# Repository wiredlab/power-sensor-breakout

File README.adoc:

= Power sensor breakout board

Connect common 1S or 2S lithium battery connectors to a load via a INA219 current sensor module.

image::img/pcb-render.png[]

link:power-sensor-breakout/power-sensor-breakout.pdf[Schematic (PDF)^]

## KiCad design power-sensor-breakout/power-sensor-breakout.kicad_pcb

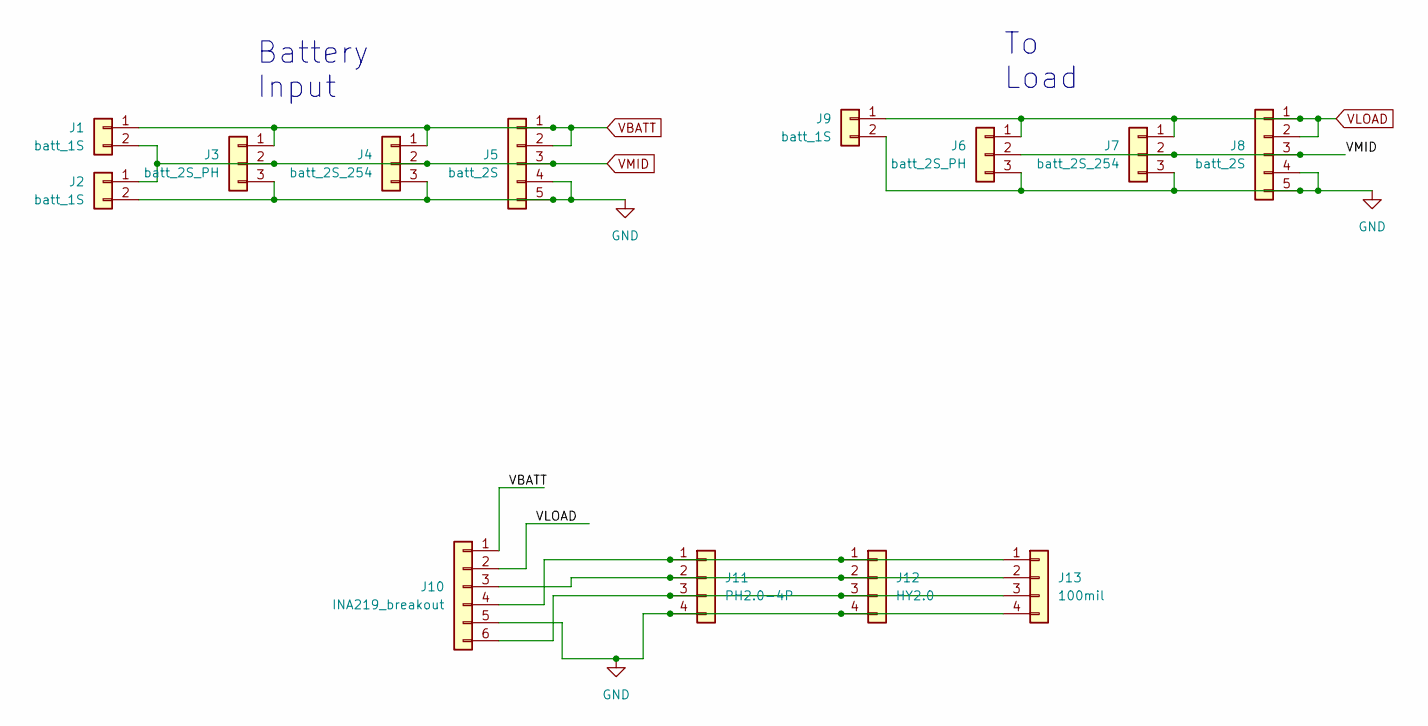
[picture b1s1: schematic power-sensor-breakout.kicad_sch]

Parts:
J1, J2, J9: batt_1S; JST_PH_B2B-PH-K_1x02_P2.00mm_Vertical
J3, J6: batt_2S_PH; JST_PH_B3B-PH-K_1x03_P2.00mm_Vertical
J4, J7: batt_2S_254; PinHeader_1x03_P2.54mm_Vertical
J5, J8: batt_2S; JST_PH_B5B-PH-K_1x05_P2.00mm_Vertical
J10: INA219_breakout; PinHeader_1x06_P2.54mm_Vertical
J11: PH2.0-4P; JST_PH_B4B-PH-K_1x04_P2.00mm_Vertical
J12: HY2.0; PinHeader_1x04_P2.00mm_Vertical
J13: 100mil; PinHeader_1x04_P2.54mm_Vertical

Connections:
GND: J2.2, J3.3, J4.3, J5.4, J5.5, J6.3, J7.3, J8.4, J8.5, J9.2, J10.5 (GND), J11.4, J12.4, J13.4
unnamed: J10.3 (SDA), J11.2, J12.2, J13.2
unnamed: J10.4 (SCL), J11.1, J12.1, J13.1
unnamed: J10.6 (VCC), J11.3, J12.3, J13.3
VBATT: J1.1, J3.1, J4.1, J5.1, J5.2, J10.1 (inp)
VLOAD: J6.1, J7.1, J8.1, J8.2, J9.1, J10.2 (inm)
VMID: J1.2, J2.1, J3.2, J4.2, J5.3, J6.2, J7.2, J8.3

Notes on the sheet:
Battery Input
To Load

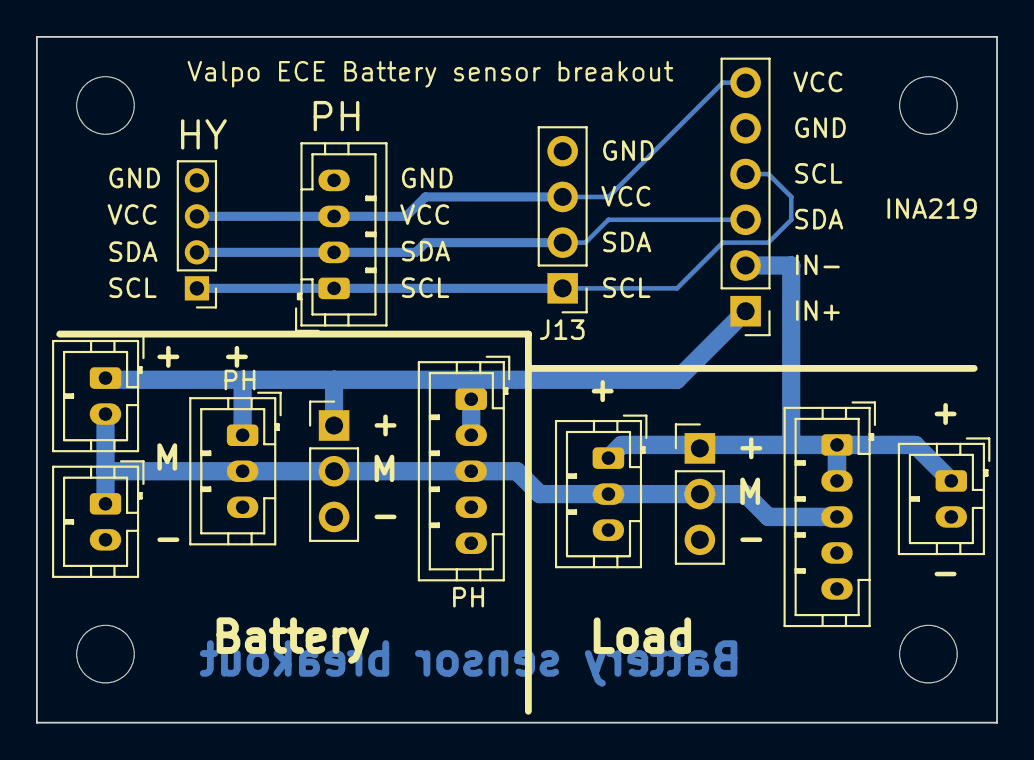
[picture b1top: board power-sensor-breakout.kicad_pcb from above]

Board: 2 copper layers, 53.3 x 38.1 mm, 17 parts (0 on the bottom side), 7 nets.

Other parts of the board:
H1, H2, H3, H4: MountingHole_3.2mm_M3

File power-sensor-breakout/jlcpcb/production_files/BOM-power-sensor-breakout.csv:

Comment,Designator,Footprint,LCSC
batt_1S,J2,JST_PH_B2B-PH-K_1x02_P2.00mm_Vertical,
batt_2S_254,J4,PinHeader_1x03_P2.54mm_Vertical,
batt_2S_PH,J3,JST_PH_B3B-PH-K_1x03_P2.00mm_Vertical,
batt_1S,J1,JST_PH_B2B-PH-K_1x02_P2.00mm_Vertical,
batt_2S,J5,JST_PH_B5B-PH-K_1x05_P2.00mm_Vertical,
batt_1S,J9,JST_PH_B2B-PH-K_1x02_P2.00mm_Vertical,
batt_2S,J8,JST_PH_B5B-PH-K_1x05_P2.00mm_Vertical,
batt_2S_254,J7,PinHeader_1x03_P2.54mm_Vertical,
batt_2S_PH,J6,JST_PH_B3B-PH-K_1x03_P2.00mm_Vertical,
100mil,J13,PinHeader_1x04_P2.54mm_Vertical,
HY2.0,J12,PinHeader_1x04_P2.00mm_Vertical,
PH2.0-4P,J11,JST_PH_B4B-PH-K_1x04_P2.00mm_Vertical,
INA219_breakout,J10,PinHeader_1x06_P2.54mm_Vertical,

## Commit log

2023-06-18 Add basic info
2023-06-18 Fix link
